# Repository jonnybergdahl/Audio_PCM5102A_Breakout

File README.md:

# Audio_PCM5102A_Breakout

This is a breakout board for the Texas Instrument PCM5102A chip. It is a I2S Audio Stereo DAC.

According to the manufacturer:

>The PCM510xA devices are a family of monolithic
CMOS-integrated circuits that include a stereo digital-to-analog converter and additional support circuitry in
a small TSSOP package.

## I2S Pins

Name | Description
---- | ----
DIN | Audio iata in
LRCK | Audio data word clock input
BCK | Audio data bit clock input
SCK | System clock inout
GND | Digital ground

## Control pins
Name | Description
---- | ----
XSMT | Soft mute control
FMT | Audio format selection
FLT | Filter select
DEMP | De-amphasis control for 44.1-kHz sampling rate

## Power
Name | Description
---- | ----
VIN | 5V power, regulated sown to 3.3V with on board LDO
EN | Enable power, 1 = On, has pullup resistor on board
GND | Ground

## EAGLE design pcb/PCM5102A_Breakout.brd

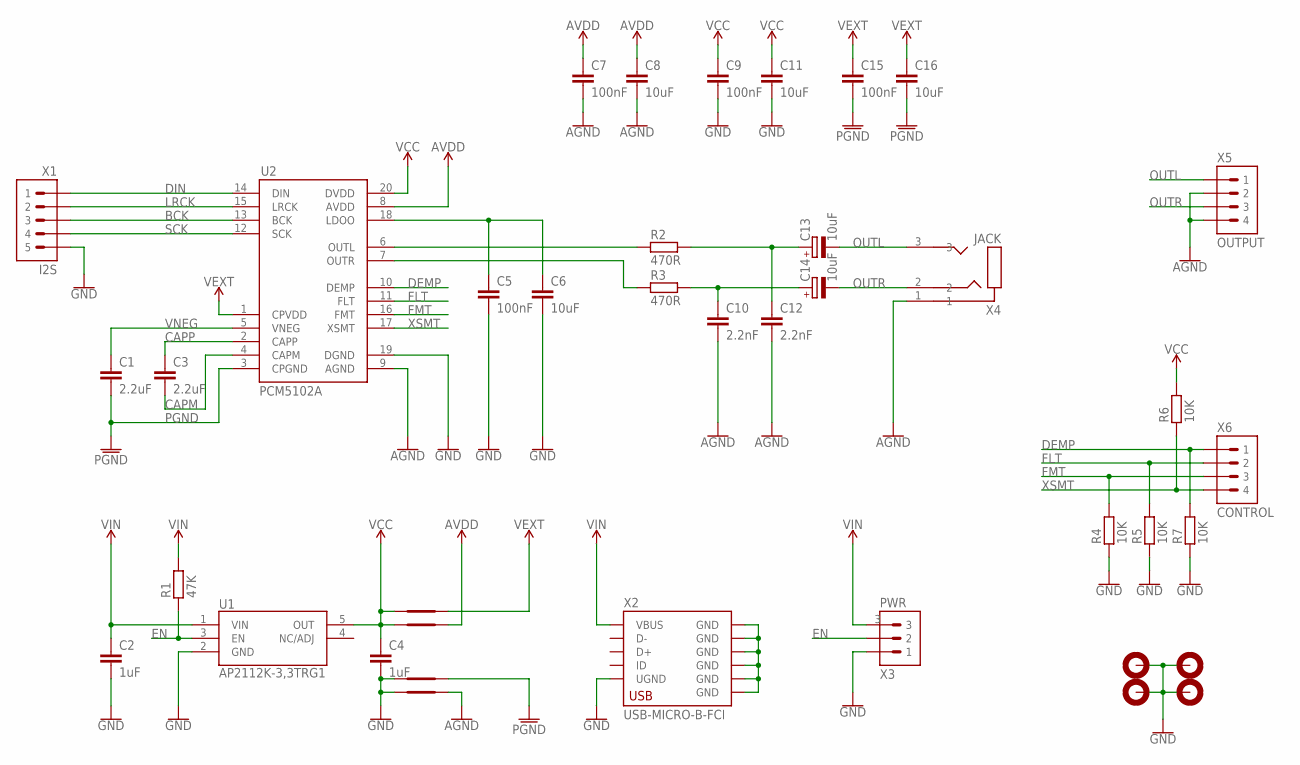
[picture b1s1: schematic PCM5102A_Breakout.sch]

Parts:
C1, C3: 2.2uF; C0603
C2, C4: 1uF; C0603
C5, C7, C9, C15: 100nF; C0603
C6, C8, C11, C16: 10uF; C0603
C10, C12: 2.2nF; C0603
C13, C14: 10uF; ROQANG-RVT0405
H1, H2, H3, H4: MOUNTHOLE-PAD3.2; 3.2-PAD
R1: 47K; R0603
R2, R3: 470R; R0603
R4, R5, R6, R7: 10K; R0603
SH1, SH2, SH3, SH4: SHORT-SMD-06096
U1: AP2112K-3,3TRG1; SOT23-5
U2: PCM5102A; TSSOP-20
X1: I2S; 1X05-2.54
X2: USB-MICRO-B-FCI
X3: PWR; 1X03P-2.54
X4: JACK; AUDIO-3.5-SJ1-3523N
X5: OUTPUT; 1X04-2.54
X6: CONTROL; 1X04-2.54

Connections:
AGND: C7.2, C8.2, C10.2, C12.2, SH4.2, U2.9 (AGND), X4.1, X5.2, X5.4
AVDD: C7.1, C8.1, SH2.2, U2.8 (AVDD)
BCK: U2.13 (BCK), X1.3
CAPM: C3.2, U2.4 (CAPM)
CAPP: C3.1, U2.2 (CAPP)
DEMP: R7.2, U2.10 (DEMP), X6.1
DIN: U2.14 (DIN), X1.1
EN: R1.1, U1.3 (EN), X3.2
FLT: R5.2, U2.11 (FLT), X6.2
FMT: R4.2, U2.16 (FMT), X6.3
GND: C2.2, C4.2, C5.2, C6.2, C9.2, C11.2, H1.B3,2, H2.B3,2, H3.B3,2, H4.B3,2, R4.1, R5.1, R7.1, SH3.1, SH4.1, U1.2 (GND), U2.19 (DGND), X1.5, X2.5 (UGND), X3.1
LRCK: U2.15 (LRCK), X1.2
unnamed: C5.1, C6.1, U2.18 (LDOO)
unnamed: R2.1, U2.6 (OUTL)
unnamed: R3.1, U2.7 (OUTR)
unnamed: C12.1, C13.+, R2.2
unnamed: C10.1, C14.+, R3.2
unnamed: X2.GND@1 (GND), X2.GND@2 (GND), X2.GND@3 (GND), X2.GND@4 (GND), X2.GND@5 (GND), X2.GND@6 (GND)
OUTL: C13.-, X4.3, X5.1
OUTR: C14.-, X4.2, X5.3
PGND: C1.2, C15.2, C16.2, SH3.2, U2.3 (CPGND)
SCK: U2.12 (SCK), X1.4
VCC: C4.1, C9.1, C11.1, R6.2, SH1.1, SH2.1, U1.5 (OUT), U2.20 (DVDD)
VEXT: C15.1, C16.1, SH1.2, U2.1 (CPVDD)
VIN: C2.1, R1.2, U1.1 (VIN), X2.1 (VBUS), X3.3
VNEG: C1.1, U2.5 (VNEG)
XSMT: R6.1, U2.17 (XSMT), X6.4

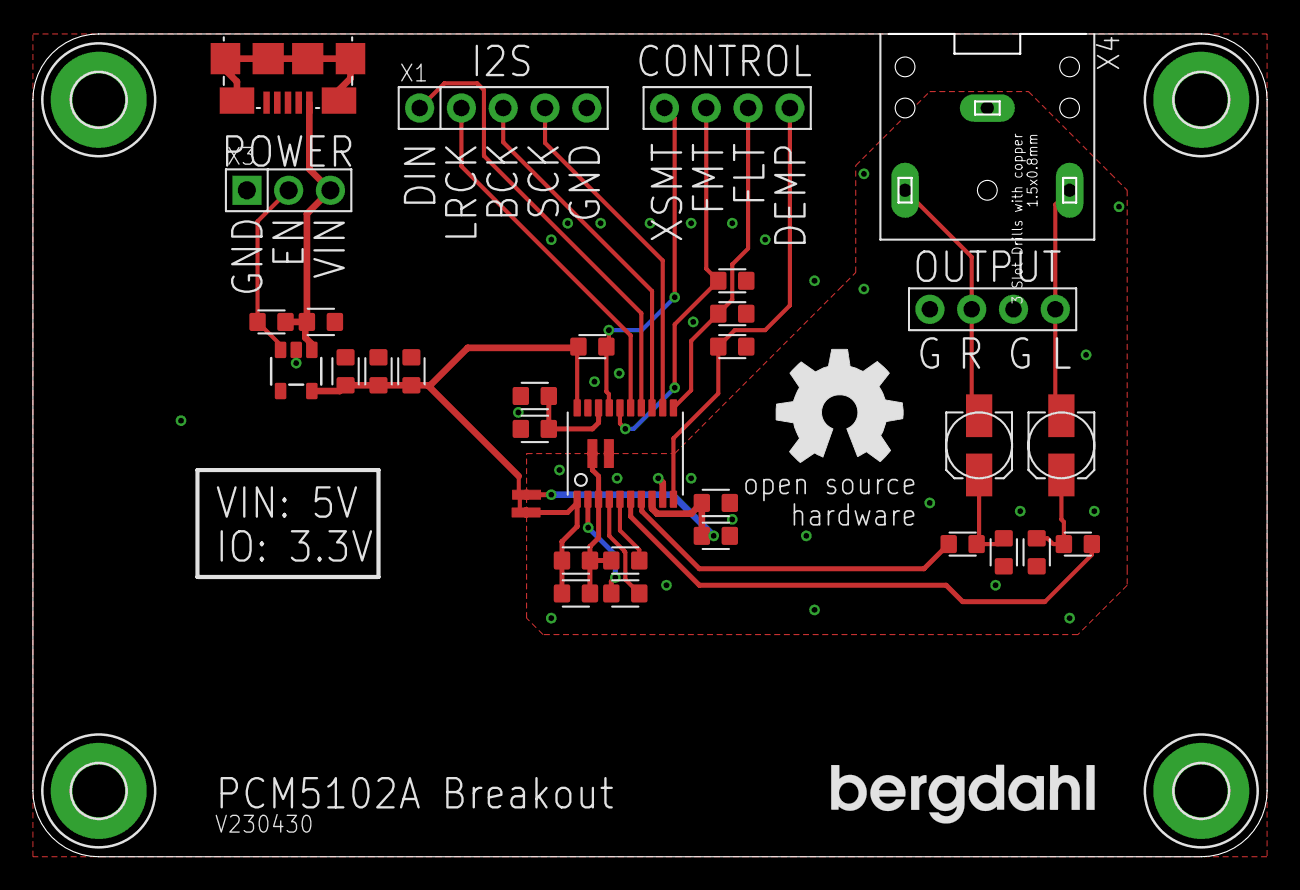
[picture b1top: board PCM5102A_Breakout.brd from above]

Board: 2 copper layers, 75.0 x 50.0 mm, 41 parts (0 on the bottom side), 27 nets.

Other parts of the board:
U$1: BERGDAHL-20MM-TPLACE
U$2: OSHW-8MM-TPLACE

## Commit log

2023-04-30 Fix speeling
2023-04-30 Update PDF
2023-05-04 Add BOM file
